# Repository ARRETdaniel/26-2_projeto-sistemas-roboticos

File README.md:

# Projeto de Sistemas Robóticos - 2026/2

Entregas da disciplina **Projeto de Sistemas Robóticos**, DCC/UFMG,
2.º semestre de 2026 (Prof. Paulo Rezeck).

**Autor:** Daniel Terra Gomes - Pós-graduação, PPGCC/DCC/UFMG

---

## Relatórios

| # | Módulo | Relatório | Estado |
|---|---|---|---|
| **R1** | Mecânica e fabricação digital | [`Relatório 1 + Métodos generativos para novos padrões de transmissão`](r1_mecanica/relatorio/relatorio1.pdf) | entregue |
| **R2** | Eletrônica e PCB | [`Relatório 2 + Roteamento e EDA assistido por LLM`](r2_eletronica_PCB/relatorio/relatorio2.pdf) | entregue |
| R3 | Embarcado, sensores e filtragem | — | — |
| R4 | Controle e odometria | — | — |
| R5 | ROS, navegação e integração | — | — |
| Extra | Sensor de distância por infravermelho (Aula 13) | [`Relatório TCRT5000`](rExtra_infravermelho/relatorio/main.pdf) | entrega 08/10 |

---

## R1 - Caixa planetária de um estágio

Projeto, modelagem paramétrica e fabricação em FDM de uma caixa de engrenagens
planetária de um estágio: sol, três planetas, coroa interna e porta-satélites.

**[→ Relatório completo (PDF)](r1_mecanica/relatorio/relatorio1.pdf)**

| Grandeza | Valor |
|---|---|
| Módulo `m` | 1,5 mm |
| Dentes — sol / planeta / anel | 12 / 18 / 48 |
| Número de planetas `n` | 3 |
| Relação de transmissão `i` | 5 (anel fixo, entrada no sol, saída no porta-satélites) |
| Folga de dente `δ` | 0,30 mm por engrenamento |
| Material / máquina | Creality Hyper PETG · Creality K1C |

### O que este trabalho tem de característico

- **Modelo integralmente dirigido por planilha.** Nenhuma cota é digitada na
  geometria: todas as propriedades das quatro peças estão ligadas por expressão
  a um alias da planilha do FreeCAD. Alterar `Zs` faz `Zr` e `i` mudarem
  sozinhos.
- **41 verificações automáticas** — 13 sobre o sólido BRep e 28 sobre a malha
  exportada — incluindo uma varredura de interferência ao longo de um ciclo
  completo de dente (volume comum nulo em todas as posições).
- **Construção por script.** O modelo e as suas verificações são reconstruíveis
  do zero a partir do que está aqui; o repositório versiona o *procedimento*,
  não apenas o resultado.
- **Sem instrumentação dimensional**, o desvio do processo foi inferido do
  comportamento do mecanismo por duas vias independentes, que convergem para
  0,11–0,12 mm por superfície. Nenhuma medida foi inventada.

### Reprodução

```bash
cd r1_mecanica
~/Applications/freecadcmd scripts/build_caixa_planetaria.py   # modelo paramétrico
~/Applications/freecadcmd scripts/export_e_valida.py          # 13 verificações + STEP/STL
~/Applications/freecadcmd scripts/valida_impressao.py         # 28 verificações de impressão
python3 scripts/busca_relacoes.py                             # busca sobre conjuntos de dentes
```

Detalhes em [`r1_mecanica/README.md`](r1_mecanica/README.md).

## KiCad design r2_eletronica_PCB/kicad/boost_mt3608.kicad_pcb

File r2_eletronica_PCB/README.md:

# Relatório 2 — Eletrônica e PCB

Conversor CC-CC elevador (*boost*) de uma célula Li-ion 1S (3,0–4,2 V) para
5,0 V, ≥ 0,5 A, com o CI MT3608. Esquemático e placa de duas camadas no
KiCad 10.0.6.

Disciplina: Projeto de Sistemas Robóticos (DCC/UFMG, 2026/2) — Prof. Paulo Rezeck.
Autor: Daniel Terra Gomes — Pós-graduação, PPGCC/DCC/UFMG.

**[Relatório (PDF)](relatorio/relatorio2.pdf)**

## Especificação atendida

| Grandeza | Valor |
|---|---|
| Entrada | 3,0–4,2 V (Li-ion 1S), contida na faixa 2–24 V do MT3608 |
| Saída | 5,000 V nominais (divisor E96 110 kΩ / 15,0 kΩ) |
| Corrente de projeto | 0,5 A contínuos |
| Ciclo de trabalho | 0,40 → 0,16 ideal; 0,487 → 0,254 com perdas (pior caso) |
| Incerteza de V_out | σ ≈ 68 mV; ±3σ em 4,834–5,163 V (dentro de ±5 %) |
| Placa | 36 × 20 mm, 2 camadas, plano de terra contínuo na inferior |
| Verificações | ERC 0 · DRC 0 · paridade esquemático–placa 0 — pela linha de comando e no editor |

## Conteúdo da entrega

Conforme a Seção 5 do enunciado:

```
relatorio/relatorio2.pdf              o relatório
kicad/boost_mt3608.kicad_pro          projeto nativo do KiCad 10
kicad/boost_mt3608.kicad_sch          esquemático
kicad/boost_mt3608.kicad_pcb          placa
bom/bom_kicad.csv                     lista de materiais
exports/esquematico/                  esquemático: etapas (símbolos, ligações) e final (PDF)
exports/pcb/                          placa: etapas, camadas superior e inferior, todas as camadas (PDF)
exports/3d/                           vista 3D (isométrica, superior, inferior)
exports/boost_mt3608_gerber.zip       Gerber + furação
exports/relatorios/                   ERC e DRC: linha de comando e editor (antes e depois da correção, ver relatório §5)
capturas/                             capturas do editor KiCad (inclui ERC/DRC antes da correção)
```

## Componentes e datasheets

| Ref. | Peça | Datasheet |
|---|---|---|
| U1 | Aerosemi MT3608 (CI de referência) | [MT3608.pdf](https://www.olimex.com/Products/Breadboarding/BB-PWR-3608/resources/MT3608.pdf) |
| L1 | Abracon ASPI-4030S-7R5M, 7,5 µH | [ASPI-4030S.pdf](https://abracon.com/Magnetics/power/ASPI-4030S.pdf) |
| D1 | Diodes Inc. B340A, Schottky 40 V 3 A, SMA | [DS30891](https://www.diodes.com/assets/Datasheets/ds30891.pdf) |
| C1–C3 | Murata GRM31CR61C226ME15, 22 µF 16 V X5R 1206 | [especificação](https://search.murata.co.jp/Ceramy/image/img/A01X/G101/ENG/GRM31CR61C226ME15-01.pdf) |
| J1 | JST B2B-PH-K-S | [catálogo PH](https://www.jst-mfg.com/product/pdf/eng/ePH.pdf) |

Alternativa avaliada: TI TPS61023 ([datasheet](https://www.ti.com/lit/ds/symlink/tps61023.pdf)).

## Abrir o projeto

KiCad 10 (os arquivos não abrem em versões anteriores). Abra
`kicad/boost_mt3608.kicad_pro`.

> O modelo 3D do footprint `L_Abracon_ASPI-4030S` não existe na biblioteca do
> KiCad 10.0.6; a placa usa o do Sunlord SWPA4030S, de dimensões idênticas
> (4,0 × 4,0 × 3,0 mm), apenas para a visualização.

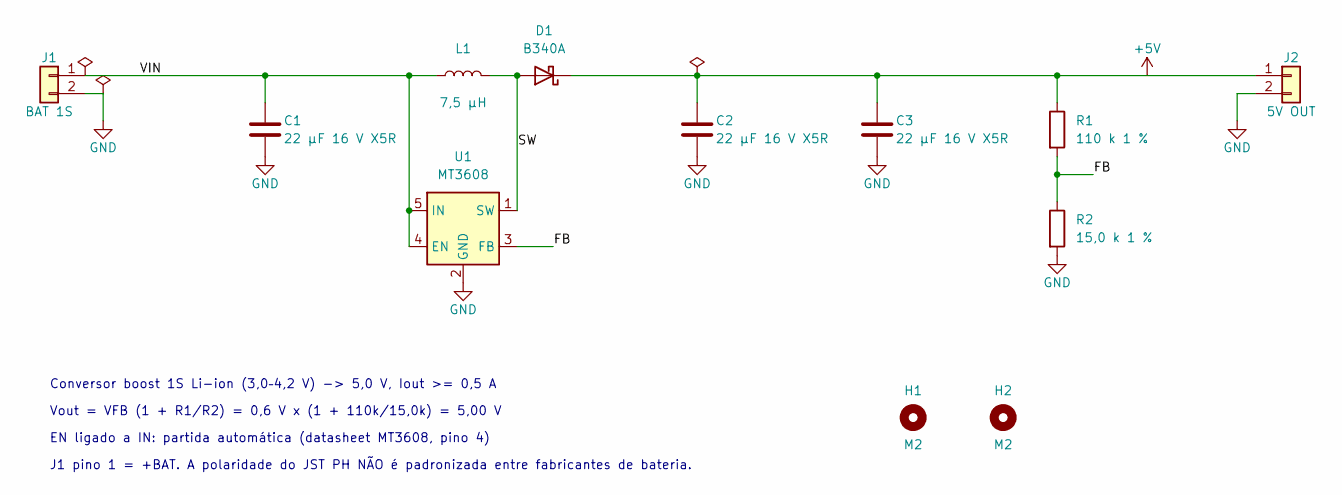
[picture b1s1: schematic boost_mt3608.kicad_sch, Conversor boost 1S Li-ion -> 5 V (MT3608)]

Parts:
C1, C2, C3: 22 µF 16 V X5R; C_1206_3216Metric; MPN GRM31CR61C226ME15L
D1: B340A; D_SMA; MPN B340A-13-F
H1, H2: M2; MountingHole_2.2mm_M2; MPN furo M2
J1: BAT 1S; JST_PH_B2B-PH-K_1x02_P2.00mm_Vertical; MPN B2B-PH-K-S
J2: 5V OUT; PinHeader_1x02_P2.54mm_Vertical; MPN header 1x02 2,54 mm
L1: 7,5 µH; L_Abracon_ASPI-4030S; MPN ASPI-4030S-7R5M-T
R1: 110 k 1 %; R_0603_1608Metric; MPN 0603, 1 %, E96
R2: 15,0 k 1 %; R_0603_1608Metric; MPN 0603, 1 %, E96
U1: MT3608; SOT-23-6; MPN MT3608

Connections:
+5V: C2.1, C3.1, D1.1 (K), J2.1, R1.1
/FB: R1.2, R2.1, U1.3 (FB)
/SW: D1.2 (A), L1.2, U1.1 (SW)
/VIN: C1.1, J1.1, L1.1, U1.4 (EN), U1.5 (IN)
GND: C1.2, C2.2, C3.2, J1.2, J2.2, R2.2, U1.2 (GND)

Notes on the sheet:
EN ligado a IN: partida automática (datasheet MT3608, pino 4)
J1 pino 1 = +BAT. A polaridade do JST PH NÃO é padronizada entre fabricantes de bateria.
Conversor boost 1S Li-ion (3,0–4,2 V) -> 5,0 V, Iout >= 0,5 A
Vout = VFB (1 + R1/R2) = 0,6 V x (1 + 110k/15,0k) = 5,00 V

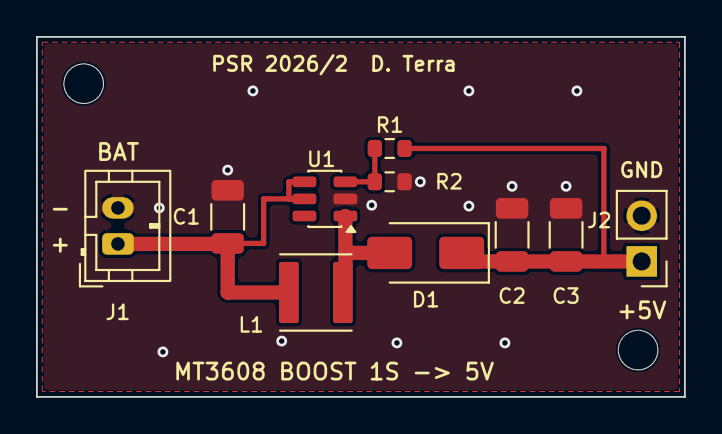
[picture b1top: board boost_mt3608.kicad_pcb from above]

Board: 2 copper layers, 36.0 x 20.0 mm, 12 parts (0 on the bottom side), 5 nets.
